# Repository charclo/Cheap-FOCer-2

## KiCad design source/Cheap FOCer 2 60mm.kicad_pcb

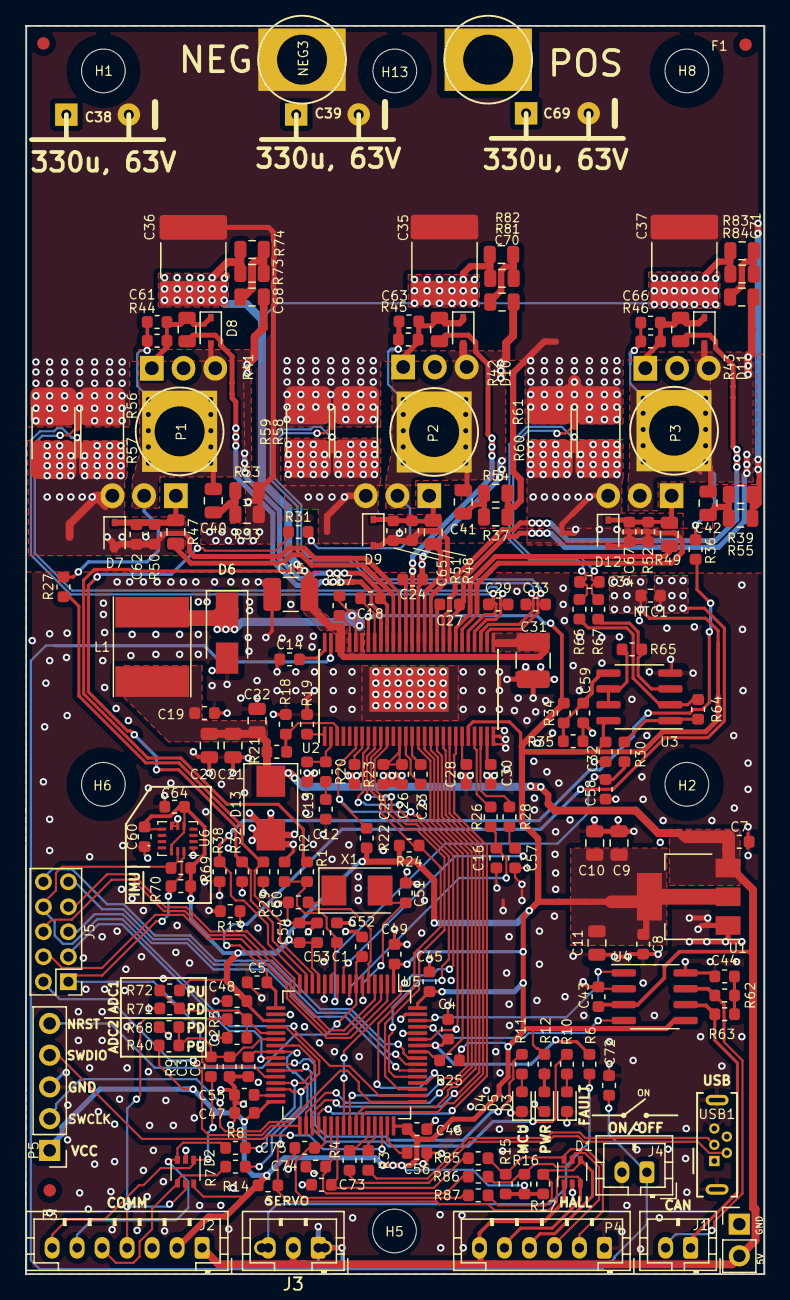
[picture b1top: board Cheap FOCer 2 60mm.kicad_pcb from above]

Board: 2 copper layers, 59.1 x 99.9 mm, 216 parts (0 on the bottom side), 126 nets.

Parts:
C1, C6, C7, C17, C32, C52, C59, C60, C64, C73, C74, C75: 100n; C_0603_1608Metric
C2, C3: 0.01uF; C_0603_1608Metric
C4: .01uF; C_0603_1608Metric
C5, C8, C45, C46, C47, C48, C49, C53, C54, C55, C56: 2.2u; C_0603_1608Metric
C9, C10, C11: 22uF; C_0805_2012Metric
C12: 6.8n; C_0603_1608Metric
C13: 150p; C_0603_1608Metric
C14: 15nF; C_0603_1608Metric
C15, C31: 4.7uF, 100V; C_1210_3225Metric_Pad1.42x2.65mm_HandSolder
C16, C29, C33, C34, C44, C57, C58, C66, C67: 1nF; C_0603_1608Metric
C18, C24, C27, C72: 220n; C_0603_1608Metric
C19, C25, C26, C28, C30: 2.2uF; C_0603_1608Metric
C20, C21, C22: 22uf; C_0805_2012Metric
C23: 22n; C_0603_1608Metric
C35, C36, C37: 10uF, 100V; C_2220_5650Metric_Pad1.97x5.40mm_HandSolder
C38, C39, C69: 330u, 63V; CP_10x20mm_hor_with_model_mirrored_less_silk
C40, C41, C42, C68, C70, C71: 4.7nF, 100V; C_0805_2012Metric
C43: 0.1u; C_0603_1608Metric
C50, C51: 15p; C_0603_1608Metric
C61, C62, C63, C65: 2.2nF; C_0603_1608Metric
D1, D2: SMF05CT1G; SOT-363_SC-70-6
D3: RED; LED_0603_1608Metric
D4: GRN; LED_0603_1608Metric
D5: BLU; LED_0603_1608Metric
D6: 100v, 1A; D_SMA
D7, D8, D9, D10, D11, D12: D_Schottky; D_SOD-323
D13: D_TVS; D_SMB
F1, F2, F3: Fiducial; Fiducial_1mm_Dia_2mm_Outer
H1, H2, H5, H6, H8, H13: MountingHole; MountingHole_3.2mm_M3_ISO14580_Pad
H3: SLJ; Sam_J
H4: Open Hardware Logo; OSHW-Logo2_9.8x8mm_SilkScreen
H9: KiCAD Logo; KiCad-Logo2_5mm_SilkScreen
J1: Conn_01x02; JST_PH_B2B-PH-K_1x02_P2.00mm_Vertical
J2: Conn_01x07; JST_PH_B7B-PH-K_1x07_P2.00mm_Vertical
J3: Conn_01x03; JST_PH_B3B-PH-K_1x03_P2.00mm_Vertical_hybrid
J4: On/Off; JST_PH_B2B-PH-K_1x02_P2.00mm_Vertical
J5: UNUSED MCU PINS; PinHeader_2x05_P2.00mm_Vertical
J6: Conn_01x03; PinHeader_1x02_P2.54mm_Vertical
L1: 22u; L_Taiyo-Yuden_NR-60xx_HandSoldering
NEG3: MOTOR3; 1pin_4mm
NT1, NT2, NT3, NT4, NT5, NT6: Net-Tie_2; NetTie-2_SMD_Pad0.5mm
NTC1: NTC 10k; R_0603_1608Metric
P1, P2, P3: MOTOR1; 1pin_4mm
P4: HALL/Encoder; JST_PH_B6B-PH-K_1x06_P2.00mm_Vertical
P5: SWD; PinHeader_1x05_P2.54mm_Vertical
POS1: POS; 1pin_4mm
Q1, Q2, Q3, Q4, Q5, Q6: NCEP60T20; TO-220-3_Horizontal_TabUp_no_hole
R1, R27, R31, R36: 39k; R_0603_1608Metric
R2, R12, R15, R16, R17, R25, R29, R32, R38: 2k2; R_0603_1608Metric
R3, R4: 22R; R_0603_1608Metric
R5, R6, R7, R8, R9, R10, R11, R85, R86, R87: 100R; R_0603_1608Metric
R13, R14, R22, R23, R34, R35, R64, R65: 10k; R_0603_1608Metric
R18: 3.3k; R_0603_1608Metric
R19: 220k; R_0603_1608Metric
R20: 15k; R_0603_1608Metric
R21: 18k; R_0603_1608Metric
R24, R66, R67, R69, R70: 1k; R_0603_1608Metric
R26, R28, R30: 1.5k; R_0603_1608Metric
R33, R37, R39, R41, R42, R43, R47, R48, R49, R53, R54, R55, R73, R74, R81, R82, R83, R84: 10R; R_0805_2012Metric
R40, R68, R71, R72: DNP; R_0603_1608Metric
R44, R45, R46, R50, R51, R52: 4.7k; R_0603_1608Metric
R56, R57, R58, R59, R60, R61: 0.001R; R_2512_Yageo_big_pads
R62, R63: 60; R_0603_1608Metric
U1: AMS1117-3.3; SOT-223-3_TabPin2
U2: DRV8301; HTSSOP-56-1EP_6.1x14mm_P0.5mm_EP3.61x6.35mm
U3: TP2604-SR; SOIC-8_3.9x4.9mm_P1.27mm
U4: TJA1051T/3/1J; SOIC-8_3.9x4.9mm_P1.27mm
U5: STM32F405RGT6; LQFP-64_10x10mm_P0.5mm
U6: BMI160; Bosch_LGA-14_3x2.5mm_P0.5mm
USB1: USB Micro U-D-M5DD-W-1; USB_Micro-B_Wuerth_614105150721_Vertical
X1: 8MHz 10ppm (X50328MSB2GI); Crystal_SMD_5032-2Pin_5.0x3.2mm

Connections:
+5V: C7.2, C19.2, C20.2, C21.2, C22.2, C43.1, D1.1, D13.1, J2.1, J3.2, J6.2, L1.2, P4.6, R21.1, U1.3, U4.3
/CAN bus transceiver/CANH: J1.2, R62.1, U4.7
/CAN bus transceiver/CANL: J1.1, R63.2, U4.6
/CAN bus transceiver/CAN_RX: U4.4, U5.61
/CAN bus transceiver/CAN_TX: U4.1, U5.62
/Filters/HALL1_IN: D1.4, P4.4, R17.1, R87.2
/Filters/HALL1_OUT: C75.2, R87.1, U5.37
/Filters/HALL2_IN: D1.5, P4.3, R16.1, R86.2
/Filters/HALL2_OUT: C74.2, R86.1, U5.38
/Filters/HALL3_IN: D1.6, P4.2, R15.1, R85.2
/Filters/TEMP_IN: C6.2, D1.3, P4.5, R14.1, U5.24
/HALL3: C73.2, R85.1, U5.39
/MCU/ADC_TEMP: C5.1, NTC1.2, R13.1, U5.17
/MCU/AN_IN: C1.2, R1.2, R2.2, U5.11
/MCU/BR_SO1: C16.2, R26.1, U5.8
/MCU/BR_SO2: C57.2, R28.1, U5.9
/MCU/BR_SO3: C58.2, R30.1, U5.10
/MCU/CS: U2.8, U5.40
/MCU/EN_GATE: R25.1, U2.16, U5.57
/MCU/FAULT: R22.2, U2.6, U5.59
/MCU/H1: U2.17, U5.41
/MCU/H2: U2.19, U5.42
/MCU/H3: U2.21, U5.43
/MCU/L1: U2.18, U5.34
/MCU/L2: U2.20, U5.35
/MCU/L3: U2.22, U5.36
/MCU/LED_GREEN: R11.2, U5.26
/MCU/LED_RED: R10.2, U5.27
/MCU/MISO_ADC_EXT2: C3.2, R9.1, R40.2, R68.2, U5.22
/MCU/RX_SDA_NSS: R7.1, U5.20, U5.30
/MCU/SCK_ADC_EXT: C2.2, R5.1, R71.2, R72.2, U5.21
/MCU/SDI: U2.9, U5.53
/MCU/SDO: R24.1, U2.10, U5.52
/MCU/SENS1: R27.2, R29.2, U5.14
/MCU/SENS2: R31.2, R32.2, U5.15
/MCU/SENS3: R36.2, R38.2, U5.16
/MCU/SERVO: C4.2, R6.1, U5.58
/MCU/SLCK: U2.11, U5.51
/MCU/TX_SCL_MOSI: R8.1, U5.23, U5.29
/MCU/USB_DM: R4.1, U5.44
/MCU/USB_DP: R3.1, U5.45
/MISO_RX_SCL_IN: D2.1, J2.7, R9.2
/Mosfet driver/GH_A: R41.2, U2.47
/Mosfet driver/GH_B: R42.2, U2.42
/Mosfet driver/GH_C: R43.2, U2.37
/Mosfet driver/GL_A: R47.2, U2.45
/Mosfet driver/GL_B: R48.2, U2.40
/Mosfet driver/GL_C: R49.2, U2.35
/Mosfet driver/H1_LOW: C62.2, D7.2, NT1.2, Q4.3, R50.2, R56.2, R57.2, U2.44
/Mosfet driver/H1_VS: C18.2, C40.1, C61.2, C68.1, D8.2, P1.1, Q1.3, Q4.2, R27.1, R44.2, U2.46
/Mosfet driver/H2_LOW: C65.2, D9.2, NT2.2, Q5.3, R51.1, R58.2, R59.2, U2.39
/Mosfet driver/H2_VS: C24.2, C41.1, C63.2, C70.1, D10.2, P2.1, Q2.3, Q5.2, R31.1, R45.1, U2.41
/Mosfet driver/H3_LOW: C67.2, D12.2, NT3.2, Q6.3, R52.1, R60.2, R61.2, U2.34
/Mosfet driver/H3_VS: C27.2, C42.1, C66.2, C71.1, D11.2, P3.1, Q3.3, Q6.2, R36.1, R46.1, U2.36
/RX_SDA_IN: D2.4, J2.5, R7.2
/SCK_ADC_EXT_IN: D2.5, J2.4, R5.2
/TX_SCL_MOSI_IN: D2.3, J2.6, R8.2
GND: C1.1, C2.1, C3.1, C4.1, C5.2, C6.1, C7.1, C8.2, C9.1, C10.1, C11.1, C12.1, C13.1, C14.2, C15.1, C16.1, C19.1, C20.1, C21.1, C22.1, C25.2, C26.2, C28.2, C30.1, C31.1, C32.1, C35.1, C36.1, C37.1, C38.2, C39.2, C43.2, C44.2, C45.1, C46.1, C47.1, C48.1, C49.1, C50.2, C51.2, C52.1, C53.1, C54.1, C55.2, C56.2, C57.1, C58.1, C59.2, C60.1, C64.1, C69.2, C72.1, C73.1, C74.1, C75.1, D1.2, D2.2, D3.1, D4.1, D5.1, D6.2, D13.2, J2.3, J3.1, J4.2, J6.1, NEG3.1, NT4.2, NT5.2, NT6.2, P4.1, P5.3, R2.1, R13.2, R18.2, R19.2, R23.1, R29.1, R32.1, R33.1, R35.2, R37.1, R38.1, R39.1, R53.1, R54.1, R55.1, R56.1, R57.1, R58.1, R59.1, R60.1, R61.1, R68.1, R71.1, U1.1, U2.28, U2.57, U3.4, U4.2, U4.8, U5.12, U5.18, U5.60, U5.63, U6.1, U6.6, U6.7, USB1.5, USB1.6
NRST: C52.2, P5.5, U5.7
unnamed: C12.2, R20.2
unnamed: C13.2, R20.1, U2.2
unnamed: C14.1, U2.56
unnamed: C17.1, U2.52
unnamed: C17.2, D6.1, L1.1, U2.50, U2.51
unnamed: C18.1, U2.48
unnamed: C23.1, U2.15
unnamed: C23.2, U2.14
unnamed: C24.1, U2.43
unnamed: C25.1, C26.1, U2.13
unnamed: C27.1, U2.38
unnamed: C28.1, U2.23
unnamed: C30.2, U2.27
unnamed: C40.2, R33.2, R53.2
unnamed: C41.2, R37.2, R54.2
unnamed: C42.2, R39.2, R55.2
unnamed: C44.1, R62.2, R63.1
unnamed: C50.1, U5.5, X1.1
unnamed: C51.1, U5.6, X1.2
unnamed: C55.1, U5.31
unnamed: C56.1, U5.47
unnamed: C59.1, R34.2, R35.1, U3.5
unnamed: C61.1, D8.1, Q1.1, R41.1, R44.1
unnamed: C62.1, D7.1, Q4.1, R47.1, R50.1
unnamed: C63.1, D10.1, Q2.1, R42.1, R45.2
unnamed: C65.1, D9.1, Q5.1, R48.1, R51.2
unnamed: C66.1, D11.1, Q3.1, R43.1, R46.2
unnamed: C67.1, D12.1, Q6.1, R49.1, R52.2
unnamed: C68.2, R73.2, R74.2
unnamed: C70.2, R81.2, R82.2
unnamed: C71.2, R83.2, R84.2
unnamed: C72.2, J4.1, U2.55
unnamed: D3.2, R10.1
unnamed: D4.2, R11.1
unnamed: D5.2, R12.1
unnamed: J3.3, R6.2
unnamed: R3.2, USB1.3
unnamed: R4.2, USB1.2
unnamed: R18.1, R21.2, U2.3
unnamed: R19.1, U2.1
unnamed: R23.2, U2.7
unnamed: R26.2, U2.25
unnamed: R28.2, U2.26
unnamed: R30.2, R64.1, U3.1
unnamed: R64.2, R66.1, U3.2
unnamed: R65.1, U3.6, U3.7
unnamed: R65.2, R67.1, U3.3
PA15: J5.8, R69.2, U5.50, U6.13
PB2: J5.1, R70.1, U5.28, U6.14
PB3: J5.9, U5.55
PB4: J5.10, U5.56
PB12: J5.2, U5.33
PC5: J5.3, U5.25
PC13: J5.4, U5.2
PC14: J5.6, U5.3
PC15: J5.7, U5.4
PD2: J5.5, U5.54
SNA: C29.2, NT1.1, U2.33
SNB: C33.1, NT2.1, U2.31
SNC: C34.1, NT3.1, R66.2
SPA: C29.1, NT4.1, U2.32
SPB: C33.2, NT5.1, U2.30
SPC: C34.2, NT6.1, R67.2
SWCLK: P5.2, U5.49
SWDIO: P5.4, U5.46
VCC: C8.1, C9.2, C10.2, C11.2, C32.2, C45.2, C46.2, C47.2, C48.2, C49.2, C53.2, C54.2, C60.2, C64.2, D2.6, J2.2, NTC1.1, P5.1, R12.2, R14.2, R15.2, R16.2, R17.2, R22.1, R24.2, R25.2, R34.1, R40.1, R69.1, R70.2, R72.1, U1.2, U2.24, U2.49, U3.8, U4.5, U5.1, U5.13, U5.19, U5.32, U5.48, U5.64, U6.5, U6.8, U6.12
V_SUPPLY: C15.2, C31.2, C35.2, C36.2, C37.2, C38.1, C39.1, C69.1, POS1.1, Q1.2, Q2.2, Q3.2, R1.1, R73.1, R74.1, R81.1, R82.1, R83.1, R84.1, U2.29, U2.53, U2.54

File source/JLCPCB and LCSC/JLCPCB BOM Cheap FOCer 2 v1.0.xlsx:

Comment | Designator | Footprint | LCSC Part # | Quantity
330u, 63V | C38, C39, C69 | CP_10x20mm_hor_with_model_mirrored_less_silk | C437643 | 3 |  | Blue highlighted componenets are not avaiable from JLCPCB's SMT service.
2.2u | C5, C8, C19, C25, C26, C28, C30, C45, C46, C47, C48, C49, C53, C54, C55, C56 | C_0603_1608Metric | C23630 | 16
100n | C1, C6, C7, C17, C32, C43, C52, C59, C60, C64, C73, C74, C75 | C_0603_1608Metric | C14663 | 13
1nF | C16, C29, C33, C34, C44, C57, C58, C66, C67 | C_0603_1608Metric | C1588 | 9
220n | C18, C24, C27, C72 | C_0603_1608Metric | C21120 | 4
2.2nF | C61, C62, C63, C65 | C_0603_1608Metric | C1604 | 4
0.01uF | C2, C3, C4 | C_0603_1608Metric | C57112 | 3
15p | C50, C51 | C_0603_1608Metric | C1644 | 2
6.8n | C12 | C_0603_1608Metric | C1631 | 1
150p | C13 | C_0603_1608Metric | C1594 | 1
15nF | C14 | C_0603_1608Metric | C1596 | 1
22n | C23 | C_0603_1608Metric | C21122 | 1
22uf | C9, C10, C11, C20, C21, C22 | C_0805_2012Metric | C45783 | 6
4.7nF, 100V | C40, C41, C42, C68, C70, C71 | C_0805_2012Metric | C21217 | 6
4.7uF, 100V | C15, C31 | C_1210_3225Metric_Pad1.42x2.65mm_HandSolder | C385986 | 2
10uF, 100V | C35, C36, C37 | C_2220_5650Metric_Pad1.97x5.40mm_HandSolder | C153035 | 3
100R | R5, R6, R7, R8, R9, R10, R11, R85, R86, R87 | R_0603_1608Metric | C22775 | 10
2k2 | R2, R12, R15, R16, R17, R25, R29, R32, R38 | R_0603_1608Metric | C4190 | 9
10k | R13, R14, R22, R23, R34, R35, R64, R65 | R_0603_1608Metric | C25804 | 8
4.7k | R44, R45, R46, R50, R51, R52 | R_0603_1608Metric | C23162 | 6
1k | R24, R66, R67, R69, R70 | R_0603_1608Metric | C21190 | 5
39k | R1, R27, R31, R36 | R_0603_1608Metric | C23153 | 4
1.5k | R26, R28, R30 | R_0603_1608Metric | C22843 | 3
22R | R3, R4 | R_0603_1608Metric | C23345 | 2
60R | R62, R63 | R_0603_1608Metric | C25196 | 2
3.3k | R18 | R_0603_1608Metric | C22978 | 1
220k | R19 | R_0603_1608Metric | C22961 | 1
15k | R20 | R_0603_1608Metric | C22809 | 1
18k | R21 | R_0603_1608Metric | C25810 | 1
10R | R33, R37, R39, R53, R54, R55, R73, R74, R81, R82, R83, R84 | R_0805_2012Metric | C17415 | 12
10R | R41, R42, R43, R47, R48, R49 | R_0805_2012Metric | C17675 | 6
0.001R | R56, R57, R58, R59, R60, R61 | R_2512_Yageo_big_pads | C76233 | 6
22u | L1 | L_Taiyo-Yuden_NR-60xx_HandSoldering | C266430 | 1
100v, 1A | D6 | D_SMA | C360437 | 1
D_TVS | D13 | D_SMB | C78395 | 1
D_Schottky | D7, D8, D9, D10, D11, D12 | D_SOD-323 | C313457 | 6
RED | D3 | LED_0603_1608Metric | C2286 | 1
GRN | D4 | LED_0603_1608Metric | C72043 | 1
BLU | D5 | LED_0603_1608Metric | C72041 | 1
SMF05CT1G | D1, D2 | SOT-363_SC-70-6 | C15879 | 2
BMI160 | U6 | Bosch_LGA-14_3x2.5mm_P0.5mm | C94021 | 1
DRV8301 | U2 | HTSSOP-56-1EP_6.1x14mm_P0.5mm_EP3.61x6.35mm | x | 1
STM32F405RGT6 | U5 | LQFP-64_10x10mm_P0.5mm | C15742 | 1
TP2604-SR | U3 | SOIC-8_3.9x4.9mm_P1.27mm | C126446 | 1
TJA1051T/3/1J | U4 | SOIC-8_3.9x4.9mm_P1.27mm | C38695 | 1
AMS1117-3.3 | U1 | SOT-223-3_TabPin2 | C6186 | 1
8MHz 10ppm (X50328MSB2GI) | X1 | Crystal_SMD_5032-2Pin_5.0x3.2mm | C115962 | 1
NTC 10k | NTC1 | R_0603_1608Metric | C76589 | 1
NCEP60T20 | Q1, Q2, Q3, Q4, Q5, Q6 | TO-220-3_Horizontal_TabUp_no_hole | C284868 | 6
USB Micro U-D-M5DD-W-1 | USB1 | USB_Micro-B_Wuerth_614105150721_Vertical | C145795 | 1
Conn_01x02 | J1 | JST_PH_B2B-PH-K_1x02_P2.00mm_Vertical | C2319 | 1
On/Off | J4 | JST_PH_B2B-PH-K_1x02_P2.00mm_Vertical | C2319 | 1
Conn_01x03 | J3 | JST_PH_B3B-PH-K_1x03_P2.00mm_Vertical_hybrid | C2320 | 1
Conn_01x07 | J2 | JST_PH_B7B-PH-K_1x07_P2.00mm_Vertical | C10398 | 1
UNUSED MCU PINS | J5 | PinHeader_2x05_P2.00mm_Vertical | C225290 | 1
HALL/Encoder | P4 | JST_PH_B6B-PH-K_1x06_P2.00mm_Vertical | C33478 | 1
SWD | P5 | PinHeader_1x05_P2.54mm_Vertical | C225480 | 1

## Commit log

2020-06-05 started redrawing pcb
2020-12-06 removed transistors from the gate of the mosfets and fixed the config file for compiling the firmware
2021-06-24 Updated 3d model
2021-06-25 Revert conf_general.h partitioning
2021-06-25 Updated Schematic and PNG's
2021-06-25 Moved component descriptors and updated ibom
2021-06-25 Added images for readme
2021-06-25 Put back Q6 which was accidentally deleted
2021-06-25 Added v0.9 and v1 support, deleted backup files
2021-06-25 Removed more backup files
2021-06-26 Deleted old BOM files
2021-06-26 Updated gerber files
2021-06-26 Removed gate transistors
2021-06-26 Revert "Remove transistors"
2021-06-26 Added the upgrade guide again
2021-06-26 Revert "Removed gate transistors"
